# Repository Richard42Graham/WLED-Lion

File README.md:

# WLED-Lion workshop and PCB files
Rev 1.1.2

This repository contains the instructions and the PCB files for a soldering and firmware flashing workshop.

Workshop page with parts information: [https://labitat.dk/wiki/Workshops/WLED-lion](https://labitat.dk/wiki/Workshops/WLED-lion)

## WLED Workshop Instructions.

### Part A - Soldering
Link: [Part A](instructions/partA.md)

### Part B - Firmware flashing
Link: [Part B](instructions/partB.md)

### Part C - Software setup and playtime
Link: [Part C](instructions/partC.md)

## Extras
A workshop participant have created a 3D model for 3D printing a box for the finished WLED-Lion LED controller, which can be found at [printables.com](https://www.printables.com/model/343865-wled-lion-box) (Licensed under CC-BY-NC).

Some more ressources:
- WLED [repository link](https://github.com/Aircoookie/WLED)
- WLED [Documentation](https://kno.wled.ge/basics/tutorials/)
- [Sound Reactive version](https://github.com/atuline/WLED) of WLED
  - Only supports ESP32
  - We recommend the INMP441 I2S digital microphone
  - Many built-in options for 2D matrices
- CH340 driver [installation instructions](https://github.com/DecaturMakers/CH340_drivers-Linux-Mac-Windows)

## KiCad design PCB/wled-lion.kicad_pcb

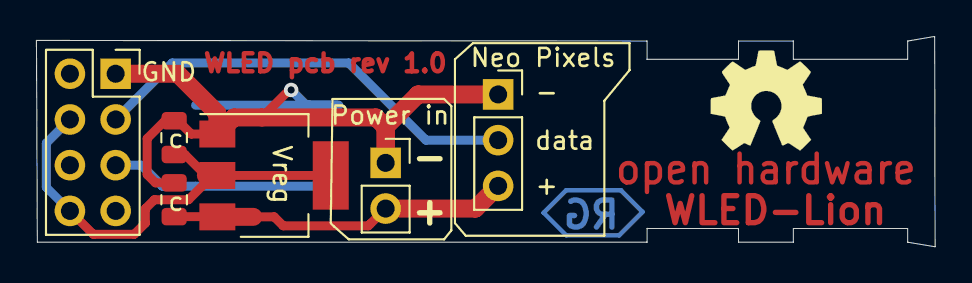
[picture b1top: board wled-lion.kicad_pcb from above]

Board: 2 copper layers, 49.9 x 11.7 mm, 7 parts (1 on the bottom side), 5 nets.

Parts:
C1, C2: C_Small; C_0805_2012Metric
J1: ESP; PinSocket_2x04_P2.54mm_Vertical
J3: Neo pixels; PinSocket_1x03_P2.54mm_Vertical
J5: Power in; PinSocket_1x02_P2.54mm_Vertical
SW1: Button; SW_Push_1P1T_NO_6x6mm_H9.5mm
U1: AMS1117-3.3; SOT-223-3_TabPin2

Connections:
+3V3: C2.1, J1.4, J1.8, U1.2 (VO)
/GPIO2: J1.3, J3.2
/GPIO-0: J1.5, SW1.2
GND: C1.2, C2.2, J1.1, J3.1, J5.1, SW1.1, U1.1 (GND)
VCC: C1.1, J3.3, J5.2, U1.3 (VI)

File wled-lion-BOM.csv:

Id,Designator,Package,Quantity,Designation,Supplier,suplyer ID
1,"C1,C2",C_0805_2012Metric,2,25uF,https://www.digikey.dk/en/products/detail/samsung-electro-me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,1276-6482-1-ND
2,J1,PinSocket_2x04_P2.54mm_Vertical,1,ESP,https://www.digikey.com/en/products/detail/sullins-connector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,S7072-ND
4,U1,SOT-223-3_TabPin2,1,AMS1117-3.3,https://www.digikey.dk/en/products/detail/texas-instruments/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,296-41282-1-ND
7,SW1,SW_Push_1P1T_NO_6x6mm_H9.5mm,1,Button,https://www.digikey.com/en/products/detail/schurter-inc/1301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,486-4184-1-ND 
,PCB,50mm X 12mm Black PCB,1,PCB,https://jlcpcb.com/,https://github.com/Richard42Graham/WLED-Lion/tree/main/ESP-Gerbers
,USB,USB-A power wire,1,USB WIRE,https://www.aliexpress.com/item/4000079448380.html,USB male to male: 
,LEDs,5M WS281X,1,Neo pixel strip,https://www.aliexpress.com/item/1005001841569840.html,
,JST,Neo pixel Connector,1,JST connector,https://de.aliexpress.com/item/32801353259.html?gatewayAdapt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,3 pin JST connector:
,ESP,ESP8266 – 01,1,ESP8266-01,https://www.aliexpress.com/item/32693314450.html,ESP01
,Programmer,USB to UART programmer,1,programmer,https://de.aliexpress.com/item/32693314450.html?gatewayAdapt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,CH340G
,zip ties,small zip ties,2,zip ties,https://de.aliexpress.com/item/4001165214623.html?spm=a2g0o.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,3 x 60mm black

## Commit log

2022-10-11 Add workshop link
2022-10-16 Add instructions
2022-10-16 move files, add troubleshoot text in instructions
2022-10-16 add MIT license
2022-10-16 add link to instruction
2022-10-20 Grammar correction
2022-10-20 decouple instruction sets
2022-10-20 correct link
2022-11-08 add programmer soldering instructions
2023-01-10 made text larger, no longer open herdware
2023-02-21 clarify binary file name
2023-02-21 rename index instruction file
2023-02-21 add missing link
2023-02-22 remove redundant backup files
2023-02-22 Split up OS instructions
2023-08-17 add NixOS esptool instructions
